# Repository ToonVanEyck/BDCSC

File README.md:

# Brushed DC Motor Servo Control

The goal of this project is to achieve precise control of a brushed DC motor using sensor less position control based on ripple counting.

# Relevant Application Notes
- [Microchip [AN3049]](https://ww1.microchip.com/downloads/en/AppNotes/Sensorless-Position-Control-of-Brushed-DC-Motor-Using-Ripple-Counting-Technique-00003049A.pdf)
- [TI [TIDA-01421]](https://www.ti.com/lit/ug/tidud30a/tidud30a.pdf?ts=1748200754762)

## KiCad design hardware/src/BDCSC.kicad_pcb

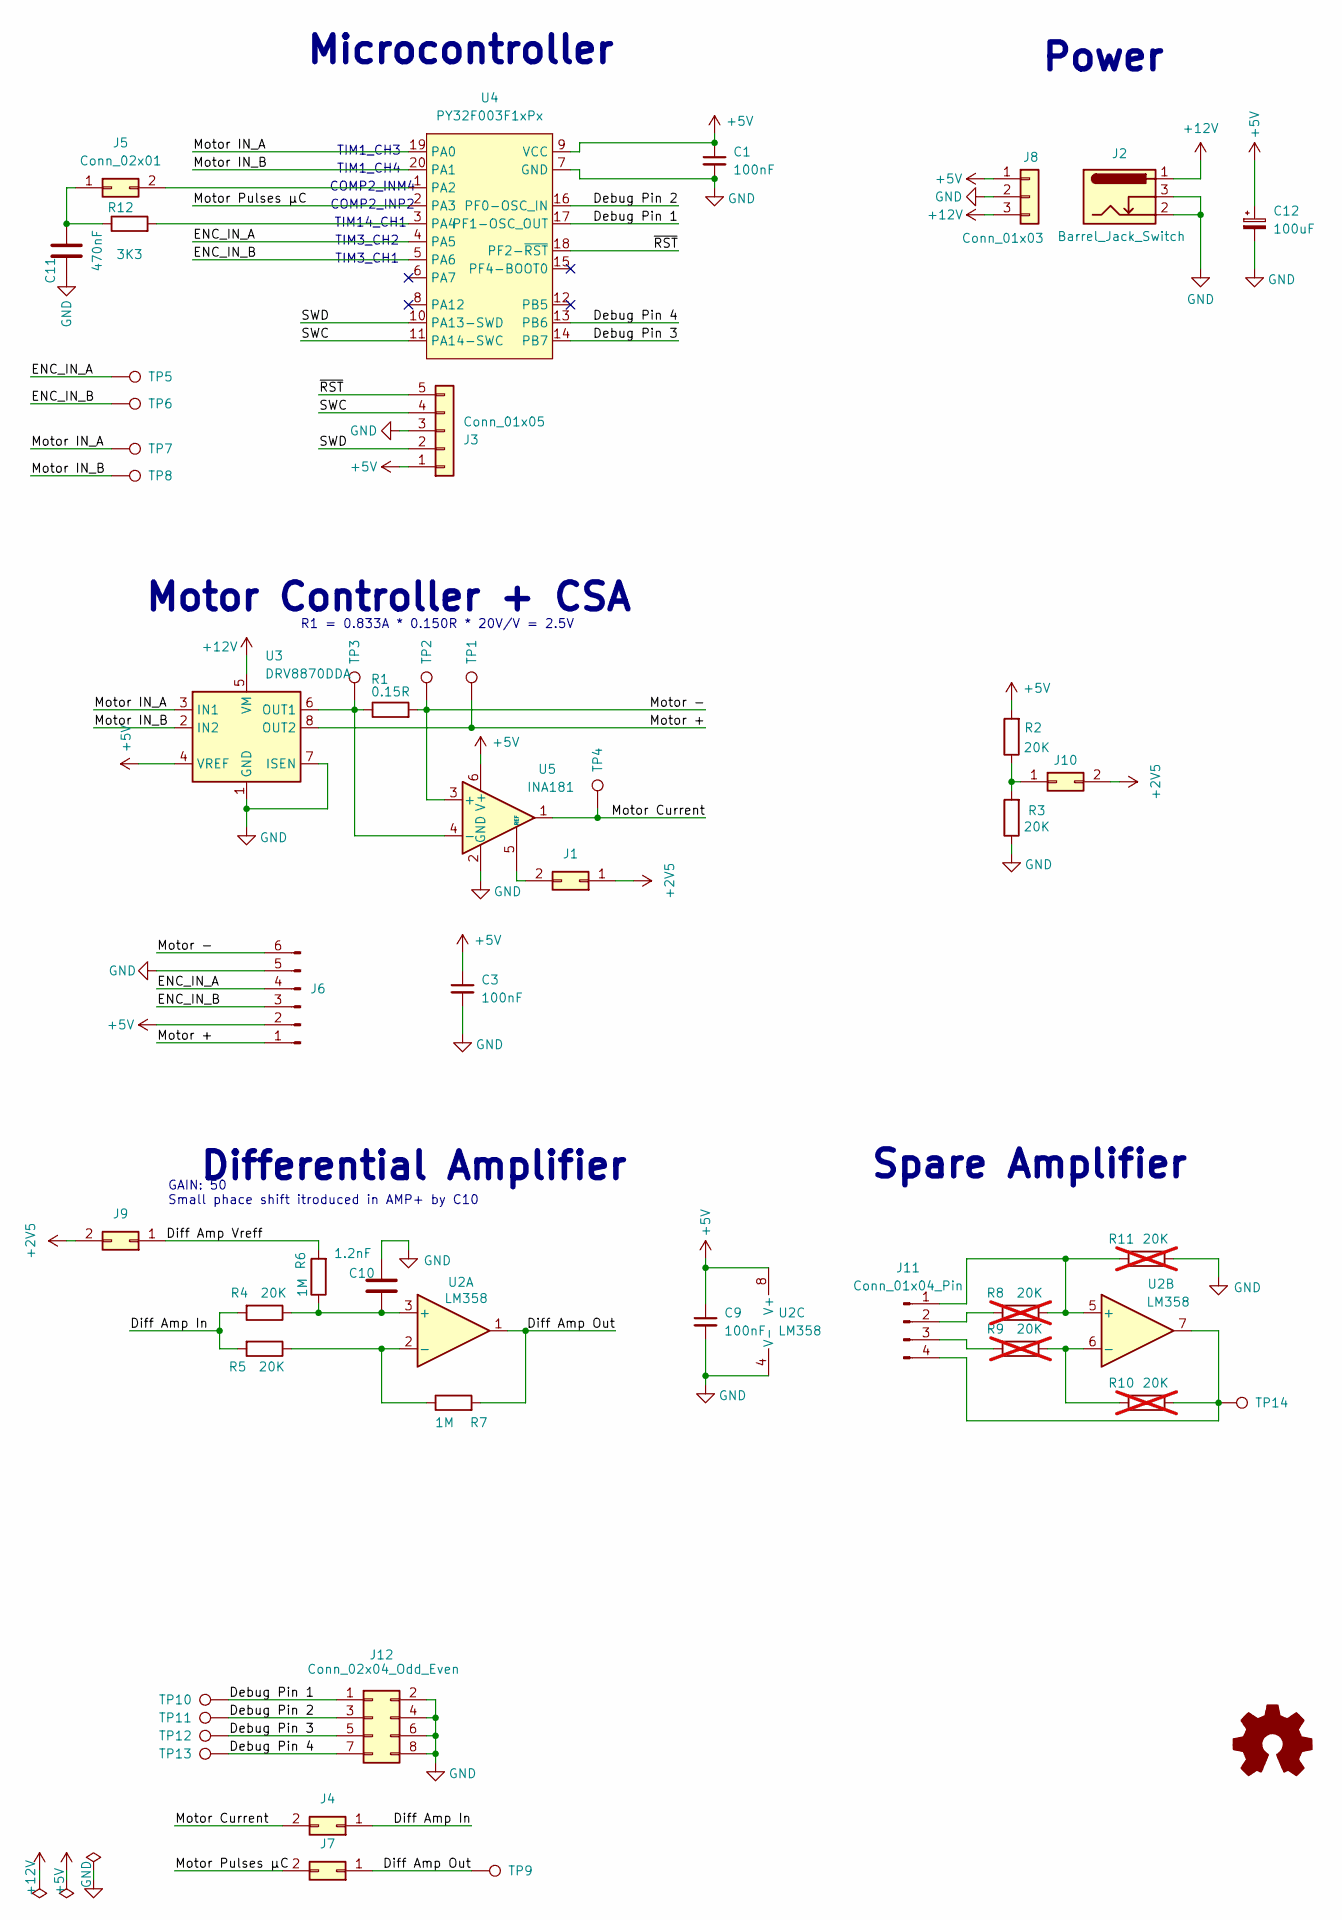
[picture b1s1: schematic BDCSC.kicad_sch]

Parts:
C1, C3, C9: 100nF; C_0805_2012Metric
C10: 1.2nF; C_0805_2012Metric
C11: 470nF; C_0805_2012Metric
C12: 100uF; CP_EIA-3528-21_Kemet-B; LCSC C16133
J1, J4, J5, J7, J9, J10: Conn_02x01; PinHeader_2x01_P2.54mm_Vertical
J2: Barrel_Jack_Switch; BarrelJack_CLIFF_FC681465S_SMT_Horizontal; LCSC C319133
J3: Conn_01x05; PinHeader_1x05_P2.54mm_Horizontal
J6: Conn_01x06_Pin; PinHeader_1x06_P2.54mm_Horizontal
J8: Conn_01x03; PinHeader_1x03_P2.54mm_Vertical
J11: Conn_01x04_Pin; PinHeader_1x04_P2.54mm_Vertical
J12: Conn_02x04_Odd_Even; PinHeader_2x04_P2.54mm_Vertical
R1: 0.15R; R_1206_3216Metric
R2, R3, R4, R5: 20K; R_0805_2012Metric
R6, R7: 1M; R_0805_2012Metric
R8, R9, R10, R11: 20K; R_0805_2012Metric; not fitted
R12: 3K3; R_0805_2012Metric
TP1, TP2, TP3, TP4, TP5, TP6, TP7, TP8, TP9, TP10, TP11, TP12, TP13, TP14: TestPoint; TestPoint_Keystone_5000-5004_Miniature; LCSC C5277086
U2: LM358; SOIC-8_3.9x4.9mm_P1.27mm
U3: DRV8870DDA; Texas_HTSOP-8-1EP_3.9x4.9mm_P1.27mm_EP2.95x4.9mm_Mask2.4x3.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
U4: PY32F003F1xPx; TSSOP-20_4.4x6.5mm_P0.65mm; LCSC C5379864
U5: INA181; SOT-23-6

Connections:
+2V5: J1.1, J9.2, J10.2
+5V: C1.1, C3.1, C9.1, C12.1, J3.1, J6.2, J8.1, R2.2, U2.8 (V+), U3.4 (VREF), U4.9 (VCC), U5.6 (V+)
+12V: J2.1, J8.3, U3.5 (VM)
/Debug Pin 1: J12.1, TP10.1, U4.17 (PF1-OSC_OUT)
/Debug Pin 2: J12.3, TP11.1, U4.16 (PF0-OSC_IN)
/Debug Pin 3: J12.5, TP12.1, U4.14 (PB7)
/Debug Pin 4: J12.7, TP13.1, U4.13 (PB6)
/Diff Amp In: J4.1, R4.2, R5.2
/Diff Amp Out: J7.1, R7.2, TP9.1, U2.1
/Diff Amp Vreff: J9.1, R6.2
/ENC_IN_A: J6.4, TP5.1, U4.4 (PA5)
/ENC_IN_B: J6.3, TP6.1, U4.5 (PA6)
/Motor +: J6.1, TP1.1, U3.8 (OUT2)
/Motor -: J6.6, R1.2, TP2.1, U5.3 (+)
/Motor Current: J4.2, TP4.1, U5.1
/Motor IN_A: TP7.1, U3.3 (IN1), U4.19 (PA0)
/Motor IN_B: TP8.1, U3.2 (IN2), U4.20 (PA1)
/Motor Pulses µC: J7.2, U4.2 (PA3)
/SWC: J3.4, U4.11 (PA14-SWC)
/SWD: J3.2, U4.10 (PA13-SWD)
/~RST: J3.5, U4.18 (PF2-~RST)
GND: C1.2, C3.2, C9.2, C10.2, C11.1, C12.2, J2.2, J2.3, J3.3, J6.5, J8.2, J12.2, J12.4, J12.6, J12.8, R3.1, R11.1, U2.4 (V-), U3.1 (GND), U3.7 (ISEN), U3.9 (GND), U4.7 (GND), U5.2 (GND)
unnamed: J1.2, U5.5 (REF)
unnamed: C11.2, J5.1, R12.1
unnamed: J5.2, U4.1 (PA2)
unnamed: J10.1, R2.1, R3.2
unnamed: J11.1, R8.1, R11.2, U2.5 (+)
unnamed: J11.2, R8.2
unnamed: J11.3, R9.2
unnamed: J11.4, R10.1, TP14.1, U2.7
unnamed: C10.1, R4.1, R6.1, U2.3 (+)
unnamed: R5.1, R7.1, U2.2 (-)
unnamed: R9.1, R10.2, U2.6 (-)
unnamed: R1.1, TP3.1, U3.6 (OUT1), U5.4 (-)
unnamed: R12.2, U4.3 (PA4)

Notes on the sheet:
Differential Amplifier
GAIN: 50 Small phace shift itroduced in AMP+ by C10
Motor Controller + CSA
TIM3_CH1
Spare Amplifier
Microcontroller
TIM3_CH2
Power
COMP2_INM4
TIM1_CH4
COMP2_INP2
TIM1_CH3
R1 = 0.833A * 0.150R * 20V/V = 2.5V
TIM14_CH1

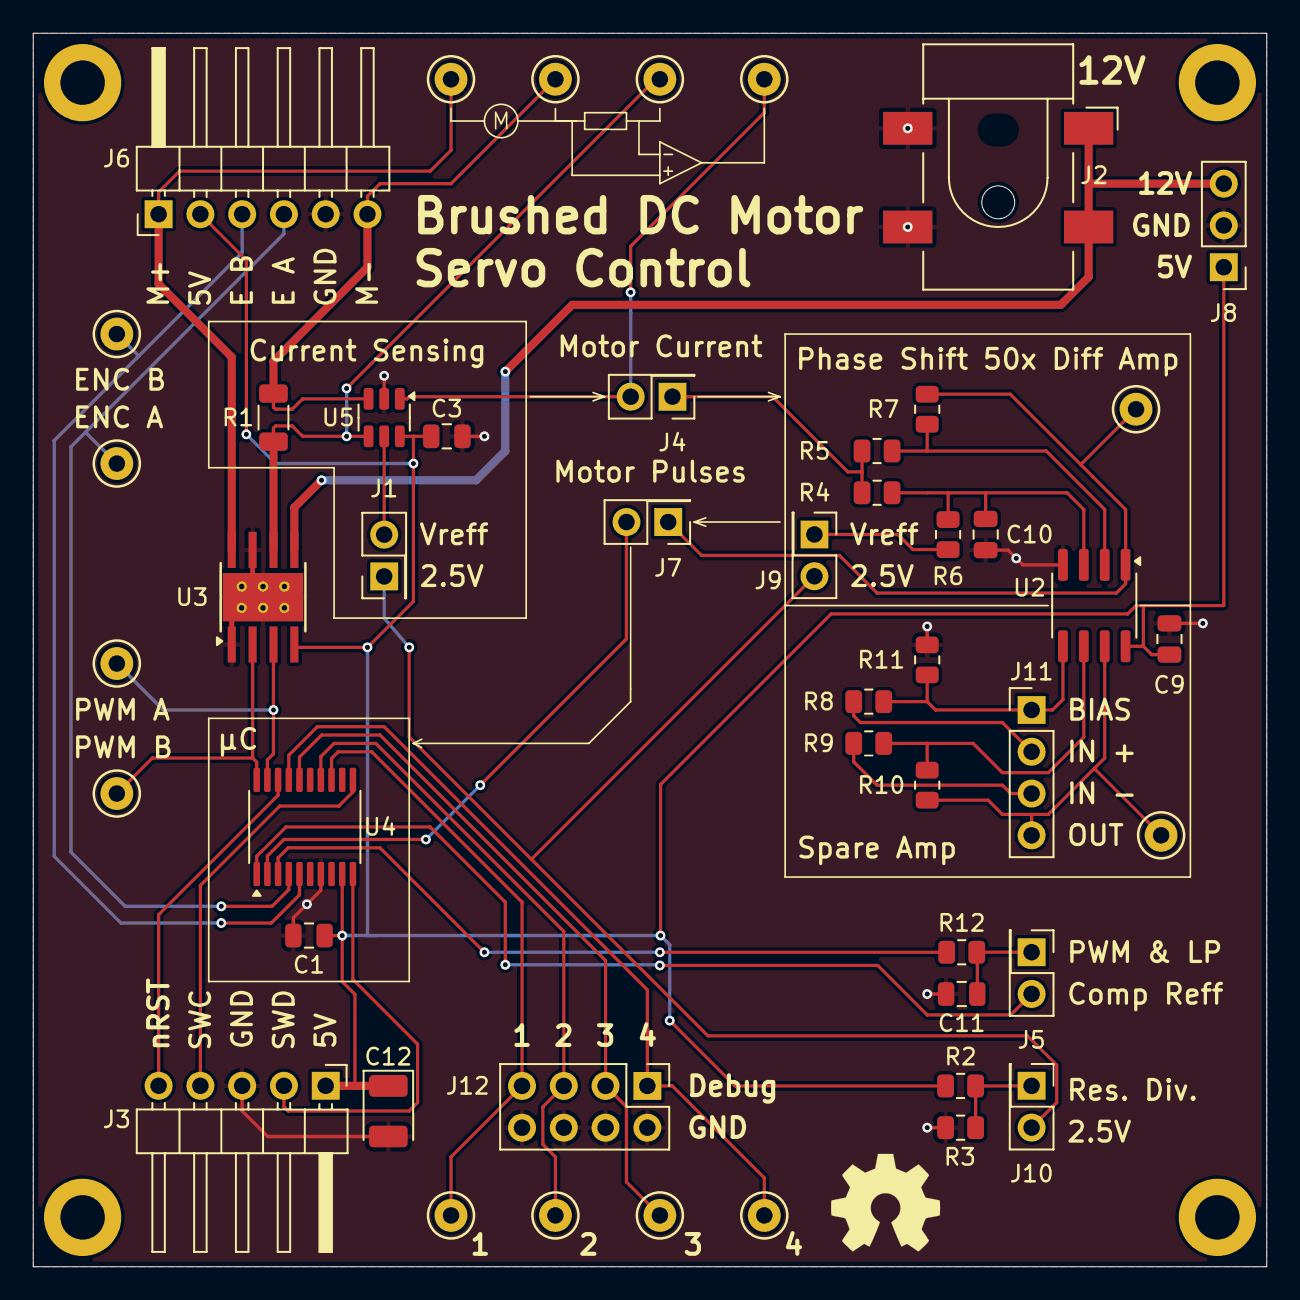
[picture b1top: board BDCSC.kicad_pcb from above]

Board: 2 copper layers, 75.0 x 75.0 mm, 48 parts (0 on the bottom side), 35 nets.

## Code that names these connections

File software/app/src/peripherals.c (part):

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    GPIO_InitStruct.Speed               = LL_GPIO_SPEED_FREQ_HIGH;
    GPIO_InitStruct.Pull                = LL_GPIO_PULL_UP;

    // Configure PA0 (TIM1_CH3) and PA1 (TIM1_CH4) as alternate function for PWM.
    // Configure PA3 (TIM1_CH1) as alternate function for Input Capture.
    GPIO_InitStruct.Pin       = LL_GPIO_PIN_0 | LL_GPIO_PIN_1 | LL_GPIO_PIN_3;
    GPIO_InitStruct.Alternate = LL_GPIO_AF_13; // TIM1_CH3 & TIM1_CH4
    LL_GPIO_Init(GPIOA, &GPIO_InitStruct);
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    // Enable TIM3 Clock
    LL_APB1_GRP1_EnableClock(LL_APB1_GRP1_PERIPH_TIM3);

    // Configure PA5 (TIM3_CH2) and PA6 (TIM3_CH1) as alternate function.
    LL_GPIO_InitTypeDef GPIO_InitStruct = {0};
    GPIO_InitStruct.Mode                = LL_GPIO_MODE_ALTERNATE;
    GPIO_InitStruct.Speed               = LL_GPIO_SPEED_FREQ_HIGH;
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
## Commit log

2025-06-17 cleanup in preparation for hardware
2025-06-20 Start om crude RTT scope for proper pid tuning and validation
2025-06-21 vibe coded rtt scope
2025-06-24 added web based rtt viewer for pid tuning
2025-07-02 Updated dev board and cad model
2025-07-02 remove vscode folder
2025-07-02 ignore vscode
